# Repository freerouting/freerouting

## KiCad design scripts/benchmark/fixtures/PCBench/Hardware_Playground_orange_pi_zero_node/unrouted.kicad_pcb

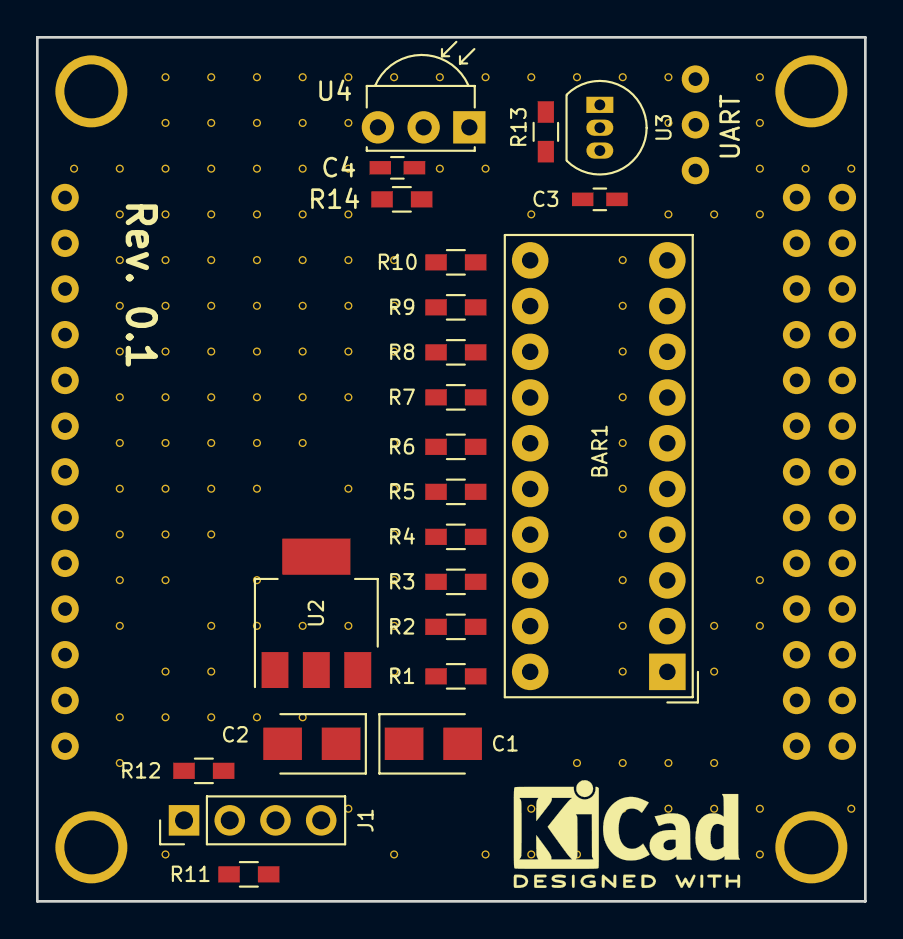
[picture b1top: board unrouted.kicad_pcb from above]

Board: 2 copper layers, 46.0 x 48.0 mm, 163 parts (0 on the bottom side), 28 nets, no tracks yet.

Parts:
BAR1: HDSP-4850_2; HDSP-4850
C1, C2: 22u; CP_Tantalum_Case-B_EIA-3528-21_Wave
C3, C4: 100n; C_0603_HandSoldering
J1: Conn_01x04; Pin_Header_Straight_1x04_Pitch2.54mm
R1, R2, R3, R4, R5, R6, R7, R8, R9, R10: 330; R_0603_HandSoldering
R11, R12, R13: 4K7; R_0603_HandSoldering
R14: 100; R_0603_HandSoldering
U1: orange_pi_zero; orangepi-zero
U2: AMS1117-3.3; SOT-223
U3: DS18B20; TO-92_Inline_Narrow_Oval
U4: TSOP343xx; IRReceiver_Vishay_MOLD-3pin
V1_3, V2_3, V2_4, V2_5, V2_6, V2_7, V2_8, V2_9, V2_10, V2_11, V2_12, V2_13, V2_15, V2_16, V3_1, V3_2, V3_3, V3_4, V3_5, V3_6, V3_7, V3_8, V3_9, V3_10, V3_11, V3_12, V3_14, V3_15, V3_18, V4_1, V4_2, V4_3, V4_4, V4_5, V4_6, V4_7, V4_8, V4_9, V4_10, V4_11, V4_13, V4_14, V4_15, V5_1, V5_2, V5_3, V5_4, V5_5, V5_6, V5_7, V5_8, V5_9, V5_10, V5_12, V5_13, V5_15, V6_1, V6_2, V6_3, V6_4, V6_5, V6_6, V6_7, V6_8, V6_9, V6_13, V6_15, V7_1, V7_2, V7_3, V7_4, V7_5, V7_6, V7_7, V7_8, V7_10, V7_13, V7_17, V8_1, V8_5, V8_6, V8_7, V8_9, V8_10, V8_11, V8_12, V8_13, V8_14, V8_18, V9_1, V9_3, V10_1, V10_3, V10_18, V11_1, V11_4, V11_17, V11_18, V12_1, V12_16, V12_17, V12_18, V13_1, V13_5, V13_6, V13_7, V13_8, V13_9, V13_10, V13_11, V13_12, V13_13, V13_14, V13_16, V13_17, V13_18, V14_1, V14_2, V14_4, V14_16, V14_17, V14_18, V15_4, V15_13, V15_14, V15_16, V15_17, V15_18, V16_1, V16_2, V16_3, V16_4, V16_12, V16_13, V16_17, V16_18, V17_3, V18_3, V18_17: AUTO_VIA; VIA_MATRIX

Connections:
+3V3: C2.1, C3.2, J1.3, R11.2, R12.2, R13.2, R14.2, U2.2, U3.3
+5V: C1.1, U1.102, U1.104, U2.3
GND: C1.2, C2.2, C3.1, C4.1, J1.4, R1.1, R2.1, R3.1, R4.1, R5.1, R6.1, R7.1, R8.1, R9.1, R10.1, U1.2, U1.106, U1.114, U1.120, U1.125, U1.201, U2.1, U3.1, U4.2, V1_3.1, V2_3.1, V2_4.1, V2_5.1, V2_6.1, V2_7.1, V2_8.1, V2_9.1, V2_10.1, V2_11.1, V2_12.1, V2_13.1, V2_15.1, V2_16.1, V3_1.1, V3_2.1, V3_3.1, V3_4.1, V3_5.1, V3_6.1, V3_7.1, V3_8.1, V3_9.1, V3_10.1, V3_11.1, V3_12.1, V3_14.1, V3_15.1, V3_18.1, V4_1.1, V4_2.1, V4_3.1, V4_4.1, V4_5.1, V4_6.1, V4_7.1, V4_8.1, V4_9.1, V4_10.1, V4_11.1, V4_13.1, V4_14.1, V4_15.1, V5_1.1, V5_2.1, V5_3.1, V5_4.1, V5_5.1, V5_6.1, V5_7.1, V5_8.1, V5_9.1, V5_10.1, V5_12.1, V5_13.1, V5_15.1, V6_1.1, V6_2.1, V6_3.1, V6_4.1, V6_5.1, V6_6.1, V6_7.1, V6_8.1, V6_9.1, V6_13.1, V6_15.1, V7_1.1, V7_2.1, V7_3.1, V7_4.1, V7_5.1, V7_6.1, V7_7.1, V7_8.1, V7_10.1, V7_13.1, V7_17.1, V8_1.1, V8_5.1, V8_6.1, V8_7.1, V8_9.1, V8_10.1, V8_11.1, V8_12.1, V8_13.1, V8_14.1, V8_18.1, V9_1.1, V9_3.1, V10_1.1, V10_3.1, V10_18.1, V11_1.1, V11_4.1, V11_17.1, V11_18.1, V12_1.1, V12_16.1, V12_17.1, V12_18.1, V13_1.1, V13_5.1, V13_6.1, V13_7.1, V13_8.1, V13_9.1, V13_10.1, V13_11.1, V13_12.1, V13_13.1, V13_14.1, V13_16.1, V13_17.1, V13_18.1, V14_1.1, V14_2.1, V14_4.1, V14_16.1, V14_17.1, V14_18.1, V15_4.1, V15_13.1, V15_14.1, V15_16.1, V15_17.1, V15_18.1, V16_1.1, V16_2.1, V16_3.1, V16_4.1, V16_12.1, V16_13.1, V16_17.1, V16_18.1, V17_3.1, V18_3.1, V18_17.1
unnamed: BAR1.1, U1.112
unnamed: BAR1.2, U1.113
unnamed: BAR1.3, U1.115
unnamed: BAR1.4, U1.116
unnamed: BAR1.5, U1.118
unnamed: BAR1.6, U1.119
unnamed: BAR1.7, U1.121
unnamed: BAR1.8, U1.122
unnamed: BAR1.9, U1.123
unnamed: BAR1.10, U1.124
unnamed: BAR1.11, R10.2
unnamed: BAR1.12, R9.2
unnamed: BAR1.13, R8.2
unnamed: BAR1.14, R7.2
unnamed: BAR1.15, R6.2
unnamed: BAR1.16, R5.2
unnamed: BAR1.17, R4.2
unnamed: BAR1.18, R3.2
unnamed: BAR1.19, R2.2
unnamed: BAR1.20, R1.2
unnamed: C4.2, R14.1, U4.3
unnamed: J1.1, R12.1, U1.103
unnamed: J1.2, R11.1, U1.105
unnamed: R13.1, U1.126, U3.2
unnamed: U1.13, U4.1

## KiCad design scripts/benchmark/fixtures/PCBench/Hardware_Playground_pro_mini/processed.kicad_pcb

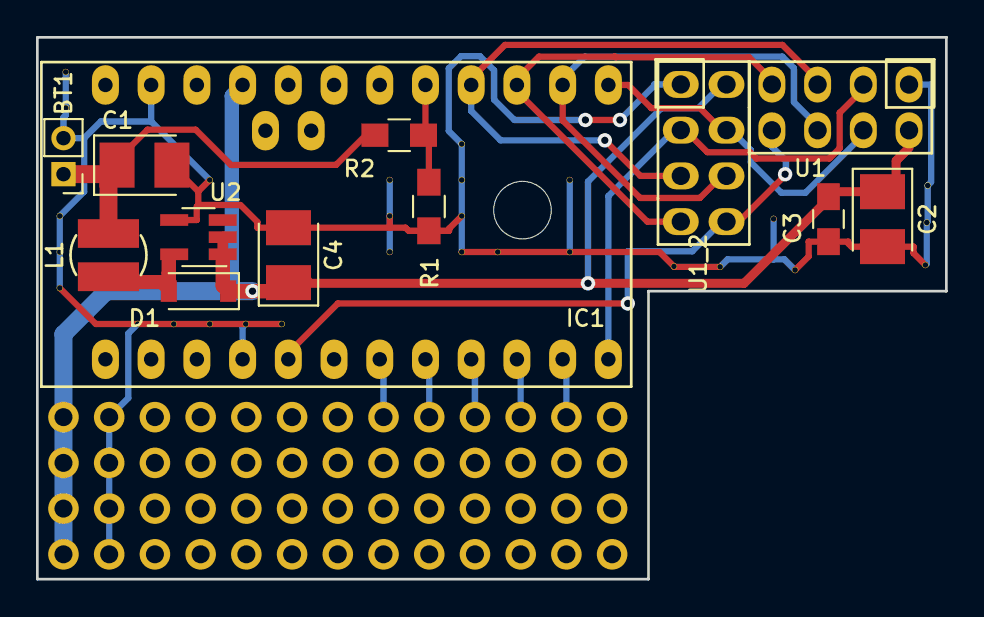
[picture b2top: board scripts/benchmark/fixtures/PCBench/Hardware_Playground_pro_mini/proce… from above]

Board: 2 copper layers, 50.5 x 30.1 mm, 41 parts (0 on the bottom side), 11 nets.

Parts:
BT1: 3V; Pin_Header_Straight_1x02_Pitch2.00mm
C1: 10u; CP_Tantalum_Case-B_EIA-3528-21_Reflow
C2: 22u; CP_Tantalum_Case-B_EIA-3528-21_Reflow
C3: 100n; C_0805_HandSoldering
C4: 68u; CP_Tantalum_Case-B_EIA-3528-21_Reflow
D1: 1N5819; D_SOD-123
IC1: ArduinoProMini; pro_mini
L1: 47u; SDR0302
R1: 10K; R_0805_HandSoldering
R2: 22K; R_0805_HandSoldering
U1, U1_2: NRF24L01
U2: NCP1402; SOT-23-5_HandSoldering
V7_1, V7_2, V7_5, V7_6, V7_7, V9_8, V10_8, V11_4, V11_8, V12_8, V13_8, V16_4, V16_5, V16_6, V18_3, V18_4, V18_5, V18_6, V18_6_2, V18_6_3, V18_6_4, V18_6_5, V18_6_6, V18_6_7, V18_6_8, V19_6, V21_4, V21_6: AUTO_VIA; VIA_MATRIX

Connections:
+3.3V: C2.1, C3.1, C4.1, D1.1, IC1.21, U1.2, U1_2.2, U2.1, U2.2
/RF_CE: IC1.12, U1.3, U1_2.3
/RF_CSN: IC1.13, U1.4, U1_2.4
/RF_IRQ: IC1.5, U1.8, U1_2.8
/RF_MISO: IC1.15, U1.7, U1_2.7
/RF_MOSI: IC1.14, U1.6, U1_2.6
/RF_SCK: IC1.16, U1.5, U1_2.5
/V_BATT: IC1.17, R1.2, R2.2
GND: BT1.2, C1.2, C2.2, C3.2, C4.2, IC1.4, IC1.23, R1.1, U1.1, U1_2.1, U2.4, V7_1.1, V7_2.1, V7_5.1, V7_6.1, V7_7.1, V9_8.1, V10_8.1, V11_4.1, V11_8.1, V12_8.1, V13_8.1, V16_4.1, V16_5.1, V16_6.1, V18_3.1, V18_4.1, V18_5.1, V18_6.1, V18_6_2.1, V18_6_3.1, V18_6_4.1, V18_6_5.1, V18_6_6.1, V18_6_7.1, V18_6_8.1, V19_6.1, V21_4.1, V21_6.1
unnamed: BT1.1, C1.1, L1.1, R2.1
unnamed: D1.2, L1.2, U2.5

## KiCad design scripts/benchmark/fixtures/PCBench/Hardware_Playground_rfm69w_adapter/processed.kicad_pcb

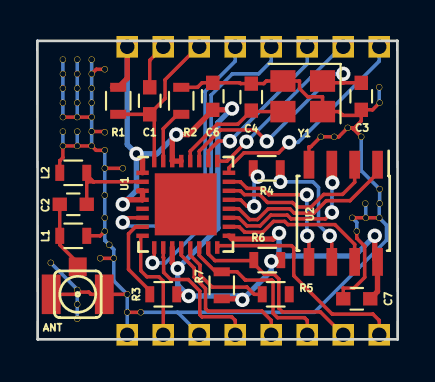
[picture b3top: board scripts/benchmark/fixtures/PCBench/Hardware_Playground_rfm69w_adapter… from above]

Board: 2 copper layers, 20.0 x 16.6 mm, 87 parts (0 on the bottom side), 29 nets.

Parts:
ANT: Antenna_Shield; coaxial_u.fl-r-smt-1
C1: 1u; C_0603
C2: 5p6; C_0603
C3, C4: 10p; C_0603
C6: 10u; C_0603
C7: 100n; C_0603
J1, J2, J3, J4, J5, J6, J7, J8, J9, J10, J11, J12, J13, J14, J15, J16: Conn_01x01; Pin_Header_Straight_1x01_Pitch2.00mm
L1, L2: DNP; L_0603
R1, R3, R5, R6, R7: 10K; R_0603
R2: 12K; R_0603
R4: 200; R_0603
U1: ESP8266EX; QFN-32-1EP_5x5mm_Pitch0.5mm
U2: AT25SF321-SSHDB; SOIC-8_3.9x4.9mm_Pitch1.27mm
V2_4, V2_5, V2_6, V2_7, V2_8, V2_9, V2_10, V3_4, V3_5, V3_6, V3_7, V3_8, V3_9, V3_10, V3_20, V3_21, V3_22, V4_4, V4_5, V4_5_2, V4_6, V4_7, V4_8, V4_9, V4_9_2, V4_10, V5_11, V5_11_2, V5_11_3, V7_21, V7_21_2, V7_21_3, V7_21_4, V7_21_5, V7_21_6, V7_21_7, V7_21_8, V7_21_9, V7_21_10, V22_9, V22_9_2, V22_9_3, V22_9_4, V22_9_5, V23_14, V23_14_2, V23_14_3, V23_14_4, V23_14_5, V24_7, V24_13, V24_14: AUTO_VIA; VIA_MATRIX
Y1: 26MHz; Crystal_SMD_3225-4pin_3.2x2.5mm

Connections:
+3V3: C6.2, C7.2, J9.1, R1.1, R3.1, R6.1, R7.1, U1.1, U1.3, U1.4, U1.11, U1.17, U1.29, U1.30, U2.8
/ADC: J15.1, U1.6
/DTR: C1.1, J13.1
/GPIO0: J8.1, R6.2, U1.15
/GPIO2: J1.1, R7.2, U1.14
/GPIO4: J2.1, U1.16
/GPIO5: J3.1, U1.24
/GPIO12: J4.1, U1.10
/GPIO13: J5.1, U1.12
/GPIO14: J6.1, U1.9
/GPIO16: J7.1, U1.8
/LNA: C2.2, L2.1, U1.2
/RESET: C1.2, J10.1, R1.2, U1.32
/SD_CLK: R4.1, U2.6
/SD_CS: U1.20, U2.1
/SD_HD: U1.18, U2.7
/SD_SI: U1.23, U2.5
/SD_SO: U1.22, U2.2
/SD_WP: U1.19, U2.3
/U0RX: J11.1, U1.26
/U0TX: J14.1, U1.25
GND: ANT.2, C3.2, C4.2, C6.1, C7.1, J12.1, J16.1, L1.2, L2.2, R2.1, U2.4, V2_4.1, V2_5.1, V2_6.1, V2_7.1, V2_8.1, V2_9.1, V2_10.1, V3_4.1, V3_5.1, V3_6.1, V3_7.1, V3_8.1, V3_9.1, V3_10.1, V3_20.1, V3_21.1, V3_22.1, V4_4.1, V4_5.1, V4_5_2.1, V4_6.1, V4_7.1, V4_8.1, V4_9.1, V4_9_2.1, V4_10.1, V5_11.1, V5_11_2.1, V5_11_3.1, V7_21.1, V7_21_2.1, V7_21_3.1, V7_21_4.1, V7_21_5.1, V7_21_6.1, V7_21_7.1, V7_21_8.1, V7_21_9.1, V7_21_10.1, V22_9.1, V22_9_2.1, V22_9_3.1, V22_9_4.1, V22_9_5.1, V23_14.1, V23_14_2.1, V23_14_3.1, V23_14_4.1, V23_14_5.1, V24_7.1, V24_13.1, V24_14.1, Y1.2, Y1.4
unnamed: ANT.1, C2.1, L1.1
unnamed: C3.1, U1.27, Y1.1
unnamed: C4.1, U1.28, Y1.3
unnamed: R2.2, U1.31
unnamed: R3.2, U1.7
unnamed: R4.2, U1.21
unnamed: R5.1, U1.13

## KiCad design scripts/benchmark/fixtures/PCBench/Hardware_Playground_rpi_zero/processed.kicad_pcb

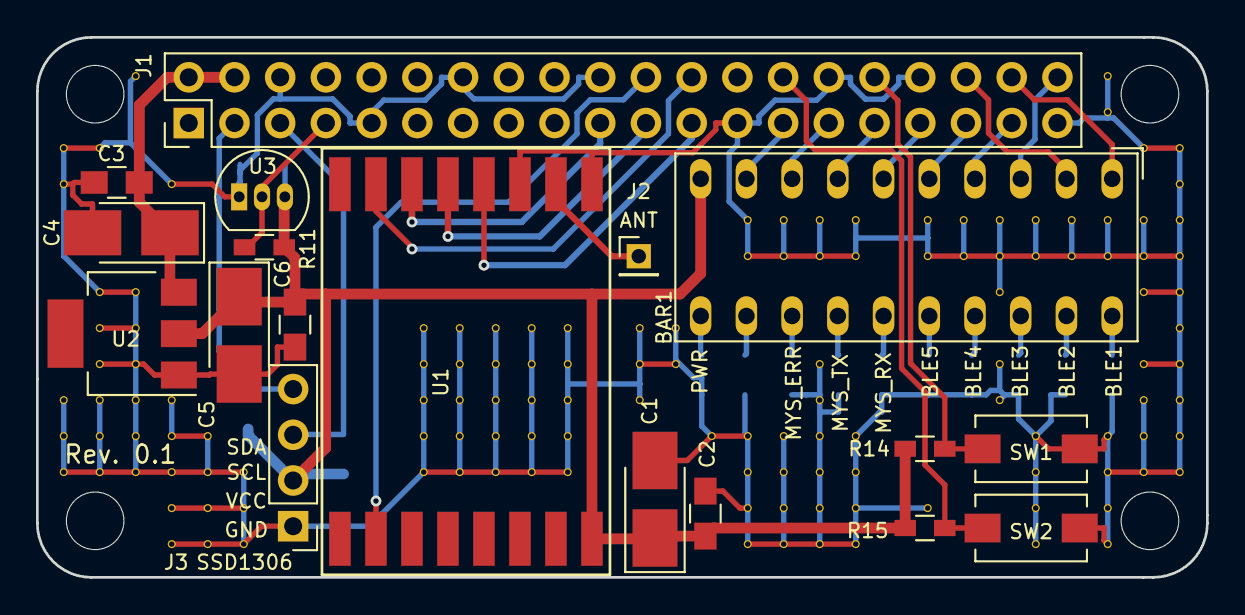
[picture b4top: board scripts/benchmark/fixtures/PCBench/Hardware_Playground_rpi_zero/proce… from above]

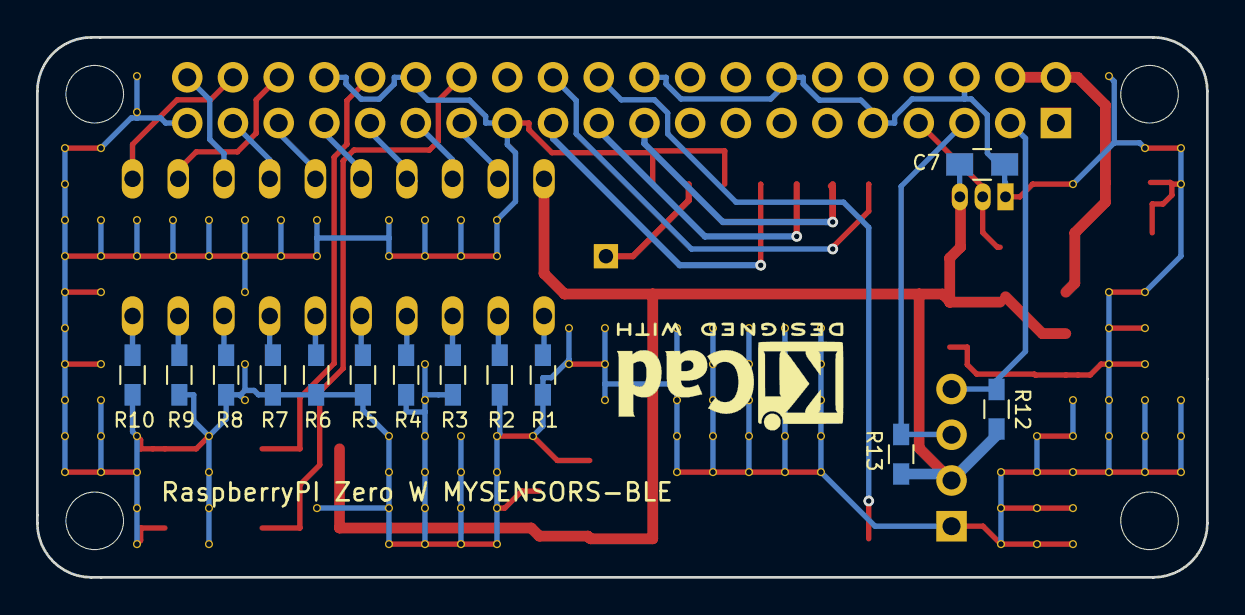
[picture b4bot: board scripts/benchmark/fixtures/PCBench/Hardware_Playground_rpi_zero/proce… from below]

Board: 2 copper layers, 65.0 x 30.0 mm, 164 parts (13 on the bottom side), 33 nets.

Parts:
BAR1: HDSP-4850_2; HDSP-4850
C1, C4, C5: 22u; CP_Tantalum_Case-B_EIA-3528-21_Hand
C2, C3, C6, C7: 100n; C_0805_HandSoldering
J1: RPI_Zero_W; Pin_Header_Straight_2x20_Pitch2.54mm
J2: ANT; Pin_Header_Straight_1x01_Pitch2.00mm
J3: SSD1306; Pin_Header_Straight_1x04_Pitch2.54mm
R1, R2, R3, R4, R5, R6, R7, R8, R9, R10: 220; R_0603_HandSoldering
R11, R12, R13: 4K7; R_0603_HandSoldering
R14, R15: 10K; R_0603_HandSoldering
SW1, SW2: BLE; SW_SPST_EVQPE1
U1: RFM69HW; RFM69HW_SMD_Handsoldering
U2: AMS1117; SOT-223
U3: DS18B20; TO-92_Inline_Narrow_Oval
V3_4, V3_5, V3_11, V3_12, V3_13, V4_4, V4_8, V4_9, V4_10, V4_11, V4_12, V4_13, V5_2, V5_8, V5_9, V5_10, V5_11, V5_12, V5_13, V6_5, V6_11, V6_12, V6_13, V6_14, V6_15, V7_12, V7_13, V7_14, V7_15, V8_13, V8_14, V8_15, V13_9, V13_10, V13_11, V13_12, V13_13, V14_9, V14_10, V14_11, V14_12, V14_13, V15_9, V15_10, V15_11, V15_12, V15_13, V16_9, V16_10, V16_11, V16_12, V16_13, V17_9, V17_10, V17_11, V17_12, V17_13, V19_9, V19_10, V19_11, V20_9, V20_10, V21_12, V22_6, V22_7, V22_12, V22_13, V22_14, V22_15, V23_6, V23_7, V23_12, V23_13, V23_14, V23_15, V24_6, V24_7, V24_10, V24_11, V24_12, V24_13, V24_14, V24_15, V25_6, V25_7, V25_12, V25_13, V25_14, V25_15, V27_6, V27_7, V27_14, V28_6, V28_7, V29_6, V29_7, V29_8, V29_10, V29_11, V30_6, V30_7, V30_12, V30_13, V30_14, V30_15, V31_6, V31_7, V32_2, V32_3, V32_6, V32_7, V32_12, V32_13, V32_14, V32_15, V33_4, V33_6, V33_7, V33_8, V33_10, V33_11, V33_12, V33_13, V34_4, V34_5, V34_6, V34_7, V34_8, V34_9, V34_10, V34_11, V34_12, V34_13: AUTO_VIA; VIA_MATRIX

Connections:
+3V3: BAR1.10, C1.1, C2.2, C5.1, C6.2, C7.1, J3.2, R11.1, R12.2, R13.2, R14.1, R15.1, U1.8, U2.2, U3.3
+5V: C3.2, C4.1, J1.2, J1.4, U2.3
/RFM69_CE: J1.22, U1.2
/RFM69_CS: J1.24, U1.15
/RFM69_MISO: J1.21, U1.13
/RFM69_MOSI: J1.19, U1.14
/RFM69_SCK: J1.23, U1.12
/SSD_SCL: J1.5, J3.3, R13.1
/SSD_SDA: J1.3, J3.4, R12.1
/SW1: J1.32, R14.2, SW1.1
/SW2: J1.28, R15.2, SW2.1
GND: C1.2, C2.1, C3.1, C4.2, C5.2, C6.1, C7.2, J1.6, J1.9, J1.14, J1.20, J1.25, J1.30, J1.34, J1.39, J3.1, R1.2, R2.2, R3.2, R4.2, R5.2, R6.2, R7.2, R8.2, R9.2, R10.2, SW1.2, SW2.2, U1.9, U1.11, U2.1, U3.1, V3_4.1, V3_5.1, V3_11.1, V3_12.1, V3_13.1, V4_4.1, V4_8.1, V4_9.1, V4_10.1, V4_11.1, V4_12.1, V4_13.1, V5_2.1, V5_8.1, V5_9.1, V5_10.1, V5_11.1, V5_12.1, V5_13.1, V6_5.1, V6_11.1, V6_12.1, V6_13.1, V6_14.1, V6_15.1, V7_12.1, V7_13.1, V7_14.1, V7_15.1, V8_13.1, V8_14.1, V8_15.1, V13_9.1, V13_10.1, V13_11.1, V13_12.1, V13_13.1, V14_9.1, V14_10.1, V14_11.1, V14_12.1, V14_13.1, V15_9.1, V15_10.1, V15_11.1, V15_12.1, V15_13.1, V16_9.1, V16_10.1, V16_11.1, V16_12.1, V16_13.1, V17_9.1, V17_10.1, V17_11.1, V17_12.1, V17_13.1, V19_9.1, V19_10.1, V19_11.1, V20_9.1, V20_10.1, V21_12.1, V22_6.1, V22_7.1, V22_12.1, V22_13.1, V22_14.1, V22_15.1, V23_6.1, V23_7.1, V23_12.1, V23_13.1, V23_14.1, V23_15.1, V24_6.1, V24_7.1, V24_10.1, V24_11.1, V24_12.1, V24_13.1, V24_14.1, V24_15.1, V25_6.1, V25_7.1, V25_12.1, V25_13.1, V25_14.1, V25_15.1, V27_6.1, V27_7.1, V27_14.1, V28_6.1, V28_7.1, V29_6.1, V29_7.1, V29_8.1, V29_10.1, V29_11.1, V30_6.1, V30_7.1, V30_12.1, V30_13.1, V30_14.1, V30_15.1, V31_6.1, V31_7.1, V32_2.1, V32_3.1, V32_6.1, V32_7.1, V32_12.1, V32_13.1, V32_14.1, V32_15.1, V33_4.1, V33_6.1, V33_7.1, V33_8.1, V33_10.1, V33_11.1, V33_12.1, V33_13.1, V34_4.1, V34_5.1, V34_6.1, V34_7.1, V34_8.1, V34_9.1, V34_10.1, V34_11.1, V34_12.1, V34_13.1
unnamed: BAR1.1, J1.38
unnamed: BAR1.2, J1.36
unnamed: BAR1.3, J1.40
unnamed: BAR1.4, J1.37
unnamed: BAR1.5, J1.35
unnamed: BAR1.6, J1.33
unnamed: BAR1.7, J1.31
unnamed: BAR1.8, J1.29
unnamed: BAR1.9, J1.27
unnamed: BAR1.11, R1.1
unnamed: BAR1.12, R2.1
unnamed: BAR1.13, R3.1
unnamed: BAR1.14, R4.1
unnamed: BAR1.15, R5.1
unnamed: BAR1.16, R6.1
unnamed: BAR1.17, R7.1
unnamed: BAR1.18, R8.1
unnamed: BAR1.19, R9.1
unnamed: BAR1.20, R10.1
unnamed: J1.7, R11.2, U3.2
unnamed: J2.1, U1.10
